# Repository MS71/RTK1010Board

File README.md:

# RTK1010Board

Arduino Compatible RTK1010 Board/PCB

**:exclamation: Design not finished yet :exclamation:**

### Features:

- Arduino compatibe form factor
- RTK1010 GPS receiver
- IPEX connector for onboard antennas
- backup battery
- optional SMA connector for external antennas
- optional LDO for LNA power supply
- optional ESP32-S2 for operating as base station
- optional power via USB
- optional IMU (BNO055)

### Use Cases:

#### A) Minimum RTK-1010 receiver with arduino form factor

  - RTK-1010 <-> RX/TX arduino pins
  - SMA or IPEX connector
  - LNA power by RTK-1010 (max 30mA)
  - RTK-1010 backup battery
  - *(optional)* LNA LDO (max 250mA)

#### B) Minimum RTK base station with RTK-1010 & ESP32-S2 powered by USB

  - ESP32: RTK <=> TCP bridge
  - powered by USB
  - SMA or IPEX connector
  - LNA power
  - RTK-1010 backup battery
  - *(optional)* LNA LDO (max 250mA)

#### C) Mowgli HEAD with RTK-1010, ESP32-S2 and IMU - *(TODO)*

  - ESP32: running microROS
  - VCC, GND, UART interface to YF mainboard
  - low power, sleep mode

---

[Build Manual](BuildManual.pdf)

For the [BOM](bom/README.md) take a look at the [bom folder](bom/) - *there is also an [iBOM](bom/ibom.html) available*

[RTK 1010 datasheet](https://www.locosystech.com/Templates/att/RTK-1010_datasheet_v0.7.pdf)

[Schematic](kicad/RTK1010Board.pdf)

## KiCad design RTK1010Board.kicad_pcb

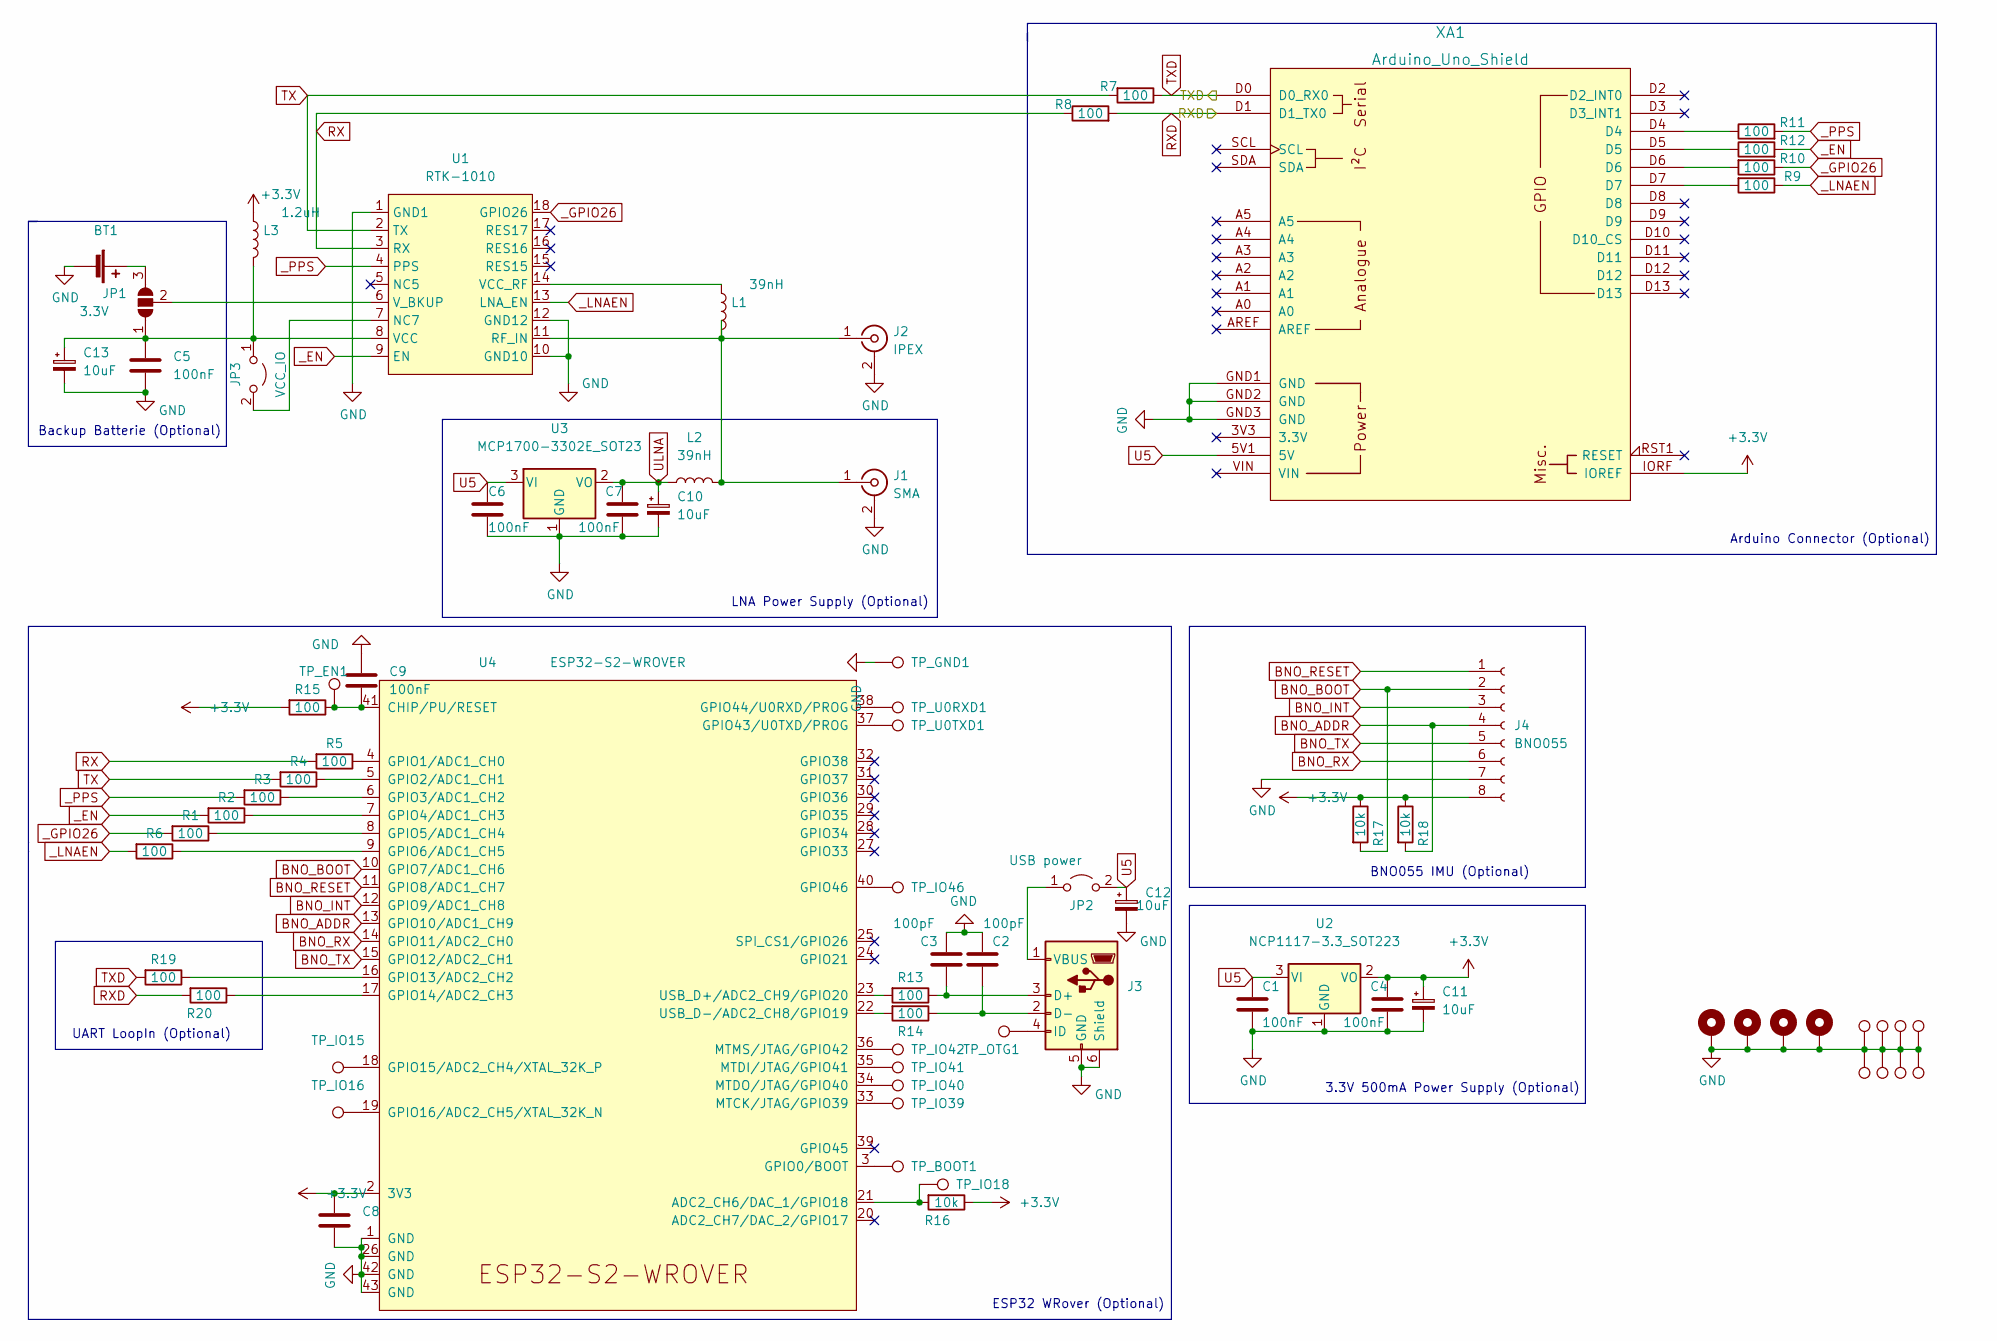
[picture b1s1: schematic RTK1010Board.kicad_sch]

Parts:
BT1: 3.3V; BatteryHolder_Keystone_1058_1x2032
C1, C4, C5, C6, C7, C8, C9: 100nF; C_0805_2012Metric_Pad1.18x1.45mm_HandSolder
C2, C3: 100pF; C_0805_2012Metric_Pad1.18x1.45mm_HandSolder
C10, C11, C12, C13: 10uF; CP_EIA-7132-20_AVX-U_Pad2.72x3.50mm_HandSolder
H1, H2, H3, H4: MountingHole_Pad; MountingHole_3.2mm_M3_DIN965_Pad
J1: SMA; SMA_Amphenol_132134-11_Vertical
J2: IPEX; U.FL_Molex_MCRF_73412-0110_Vertical
J3: USB_OTG; USB_Micro-B_Amphenol_10118194_Horizontal
J4: BNO055; PinSocket_1x08_P2.54mm_Vertical_SMD_Pin1Right
JP1: SolderJumper_3_Open; SolderJumper-3_P1.3mm_Open_RoundedPad1.0x1.5mm
JP2: USB power; SolderJumper-2_P1.3mm_Open_RoundedPad1.0x1.5mm
JP3: VCC_IO; SolderJumper-2_P1.3mm_Open_RoundedPad1.0x1.5mm
L1, L2: 39nH; L_0805_2012Metric_Pad1.15x1.40mm_HandSolder
L3: 1.2uH; L_0805_2012Metric_Pad1.15x1.40mm_HandSolder
R1, R2, R3, R4, R5, R6, R7, R8, R9, R10, R11, R12, R13, R14, R15, R19, R20: 100; R_0805_2012Metric_Pad1.20x1.40mm_HandSolder
R16, R17, R18: 10k; R_0805_2012Metric_Pad1.20x1.40mm_HandSolder
TP1, TP2, TP3, TP4, TP5, TP6, TP7, TP8: TestPoint; TestPoint_Loop_D2.50mm_Drill1.0mm
TP_BOOT1: TestPoint; TestPoint_Pad_D2.0mm
TP_EN1: TestPoint; TestPoint_Pad_D2.0mm
TP_GND1: TestPoint; TestPoint_Pad_D2.0mm
TP_IO15, TP_IO16, TP_IO18, TP_IO39, TP_IO40, TP_IO41, TP_IO42, TP_IO46: TestPoint; TestPoint_Pad_D2.0mm
TP_OTG1: TestPoint; TestPoint_Pad_D2.0mm
TP_U0RXD1, TP_U0TXD1: TestPoint; TestPoint_Pad_D2.0mm
U1: RTK-1010; rtk1010
U2: NCP1117-3.3_SOT223; SOT-223-3_TabPin2
U3: MCP1700-3302E_SOT23; SOT-23
U4: ESP32-S2-WROVER
XA1: Arduino_Uno_Shield

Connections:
+3V3: C4.1, C8.1, C11.1, J4.8, L3.1, R15.2, R16.1, R17.1, R18.1, U2.2 (VO), U4.2 (3V3), XA1.IORF (IOREF)
BNO_ADDR: J4.4, R18.2, U4.13 (GPIO10/ADC1_CH9)
BNO_BOOT: J4.2, R17.2, U4.10 (GPIO7/ADC1_CH6)
BNO_INT: J4.3, U4.12 (GPIO9/ADC1_CH8)
BNO_RESET: J4.1, U4.11 (GPIO8/ADC1_CH7)
BNO_RX: J4.6, U4.14 (GPIO11/ADC2_CH0)
BNO_TX: J4.5, U4.15 (GPIO12/ADC2_CH1)
GND: BT1.2 (-), C1.2, C2.1, C3.1, C4.2, C5.2, C6.2, C7.2, C8.2, C9.1, C10.2, C11.2, C12.2, C13.2, H1.1, H2.1, H3.1, H4.1, J1.2 (Ext), J2.2 (Ext), J3.5 (GND), J3.6 (Shield), J4.7, TP1.1, TP2.1, TP3.1, TP4.1, TP5.1, TP6.1, TP7.1, TP8.1, TP_GND1.1, U1.1 (GND1), U1.10 (GND10), U1.12 (GND12), U2.1 (GND), U3.1 (GND), U4.1 (GND), U4.26 (GND), U4.42 (GND), U4.43 (GND), XA1.GND1 (GND), XA1.GND2 (GND), XA1.GND3 (GND)
unnamed: BT1.1 (+), JP1.3 (B)
unnamed: C2.2, J3.2 (D-), R14.1
unnamed: C3.2, J3.3 (D+), R13.1
unnamed: C9.2, R15.1, TP_EN1.1, U4.41 (CHIP/PU/RESET)
unnamed: C5.1, C13.1, JP1.1 (A), JP3.1 (A), L3.2, U1.8 (VCC)
unnamed: J1.1 (In), J2.1 (In), L1.2, L2.2, U1.11 (RF_IN)
unnamed: J3.1 (VBUS), JP2.1 (A)
unnamed: J3.4 (ID), TP_OTG1.1
unnamed: JP1.2 (C), U1.6 (V_BKUP)
unnamed: JP3.2 (B), U1.7 (NC7)
unnamed: L1.1, U1.14 (VCC_RF)
unnamed: R1.1, U4.8 (GPIO5/ADC1_CH4)
unnamed: R2.1, U4.7 (GPIO4/ADC1_CH3)
unnamed: R3.1, U4.6 (GPIO3/ADC1_CH2)
unnamed: R4.1, U4.5 (GPIO2/ADC1_CH1)
unnamed: R5.1, U4.4 (GPIO1/ADC1_CH0)
unnamed: R6.1, U4.9 (GPIO6/ADC1_CH5)
unnamed: R9.2, XA1.D7
unnamed: R10.2, XA1.D6
unnamed: R11.1, XA1.D4
unnamed: R12.1, XA1.D5
unnamed: R13.2, U4.23 (USB_D+/ADC2_CH9/GPIO20)
unnamed: R14.2, U4.22 (USB_D-/ADC2_CH8/GPIO19)
unnamed: R16.2, TP_IO18.1, U4.21 (ADC2_CH6/DAC_1/GPIO18)
unnamed: R19.1, U4.16 (GPIO13/ADC2_CH2)
unnamed: R20.1, U4.17 (GPIO14/ADC2_CH3)
unnamed: TP_BOOT1.1, U4.3 (GPIO0/BOOT)
unnamed: TP_IO15.1, U4.18 (GPIO15/ADC2_CH4/XTAL_32K_P)
unnamed: TP_IO16.1, U4.19 (GPIO16/ADC2_CH5/XTAL_32K_N)
unnamed: TP_IO39.1, U4.33 (MTCK/JTAG/GPIO39)
unnamed: TP_IO40.1, U4.34 (MTDO/JTAG/GPIO40)
unnamed: TP_IO41.1, U4.35 (MTDI/JTAG/GPIO41)
unnamed: TP_IO42.1, U4.36 (MTMS/JTAG/GPIO42)
unnamed: TP_IO46.1, U4.40 (GPIO46)
unnamed: TP_U0RXD1.1, U4.38 (GPIO44/U0RXD/PROG)
unnamed: TP_U0TXD1.1, U4.37 (GPIO43/U0TXD/PROG)
RX: R5.2, R8.1, U1.3 (RX)
RXD: R8.2, R20.2, XA1.D1 (D1_TX0)
TX: R4.2, R7.2, U1.2 (TX)
TXD: R7.1, R19.2, XA1.D0 (D0_RX0)
U5: C1.1, C6.1, C12.1, JP2.2 (B), U2.3 (VI), U3.3 (VI), XA1.5V1 (5V)
ULNA: C7.1, C10.1, L2.1, U3.2 (VO)
_EN: R2.2, R12.2, U1.9 (EN)
_GPIO26: R1.2, R10.1, U1.18 (GPIO26)
_LNAEN: R6.2, R9.1, U1.13 (LNA_EN)
_PPS: R3.2, R11.2, U1.4 (PPS)

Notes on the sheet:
ESP32 WRover (Optional)
Arduino Connector (Optional)
LNA Power Supply (Optional)
3.3V 500mA Power Supply (Optional)
BNO055 IMU (Optional)
Backup Batterie (Optional)
UART LoopIn (Optional)

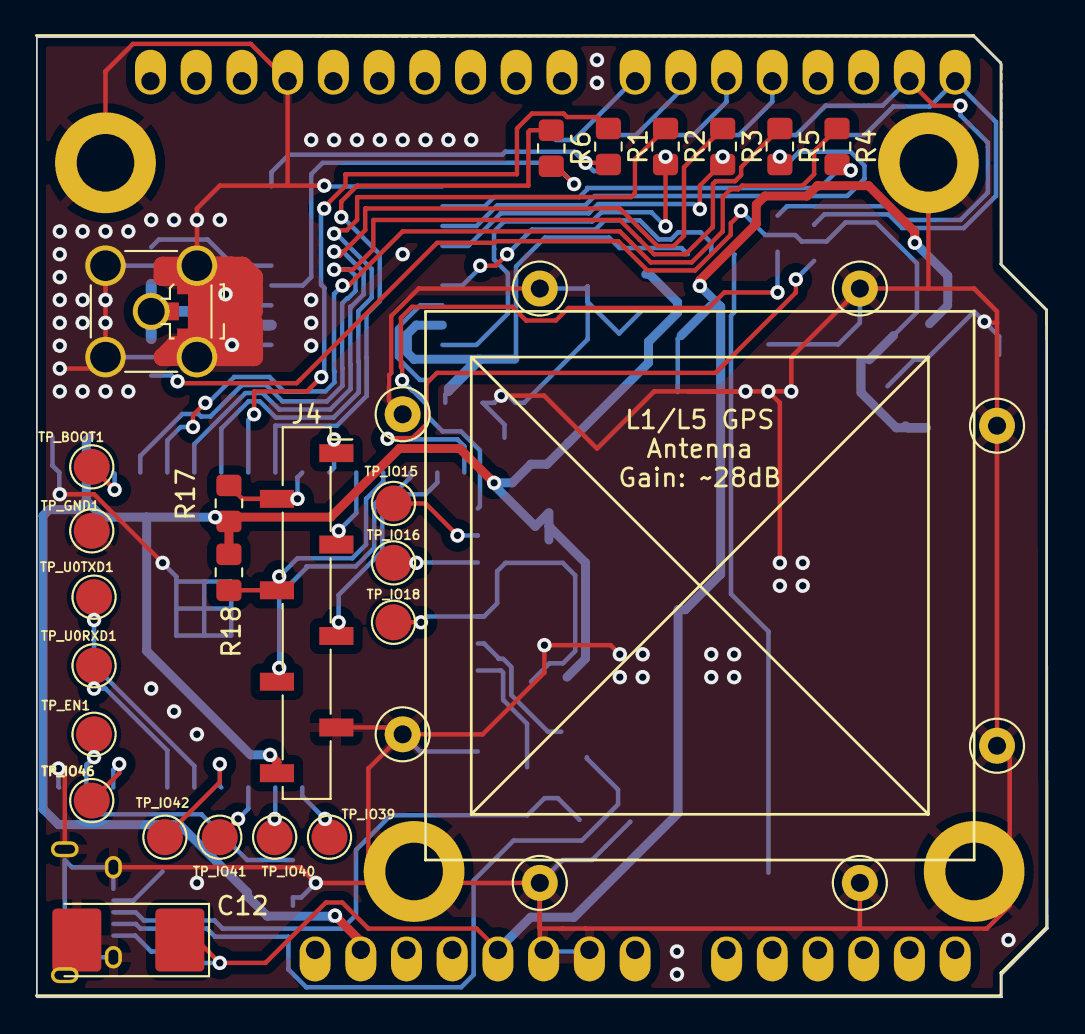
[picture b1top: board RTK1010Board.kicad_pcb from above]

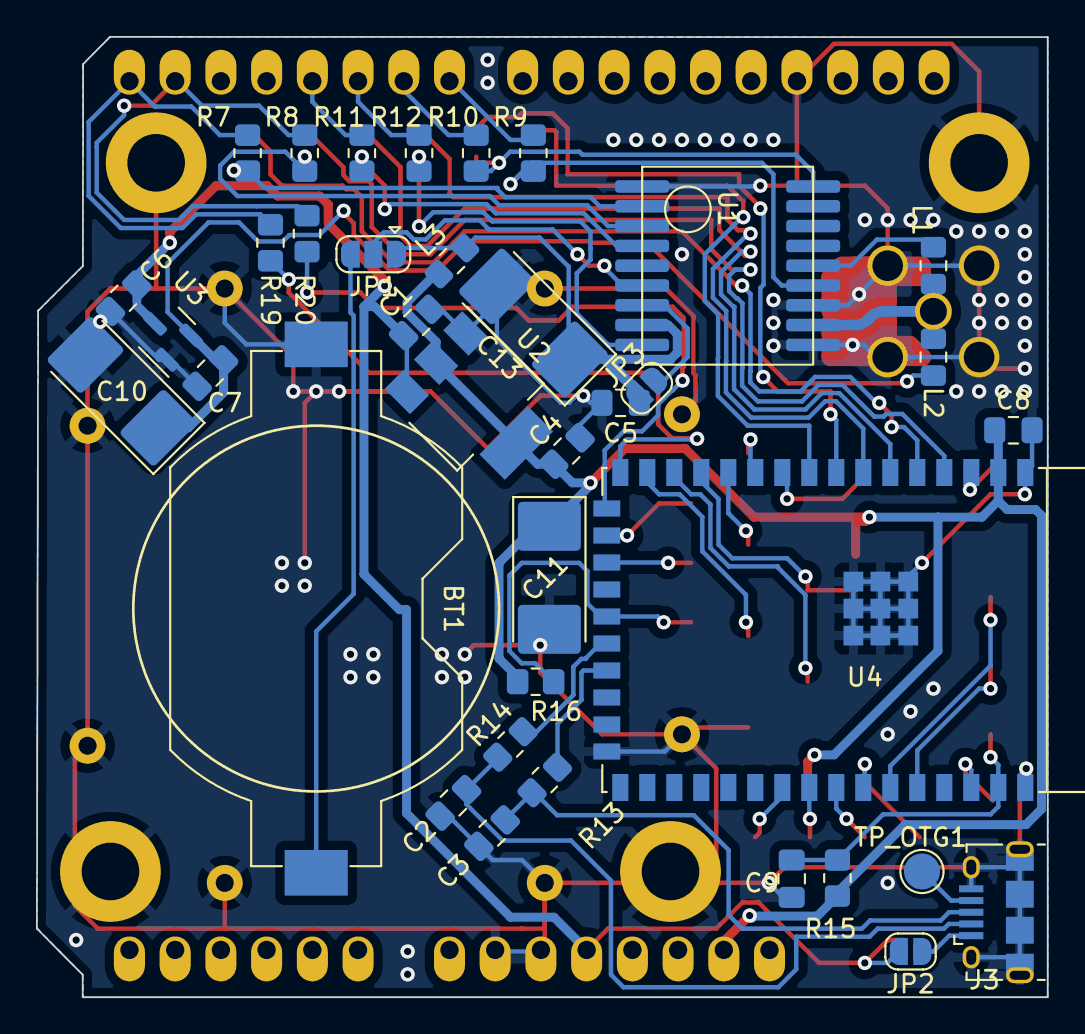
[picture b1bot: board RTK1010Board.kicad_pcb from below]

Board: 2 copper layers, 56.2 x 53.3 mm, 75 parts (37 on the bottom side), 54 nets.

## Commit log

2022-08-08 first version
2022-08-08 pdf and images added
2022-08-08 schematic image added
2022-08-08 gerber files added
2022-08-08 ESP32-S2 mini replaced by WROVER module
2022-08-08 gerber files created
2022-08-08 some more small changes
2022-08-14 bno055 added
2022-08-17 UART LoopIn option added USB connected to USB pins
2022-08-17 boot image added
2022-08-19 some optimiziations implemented
2022-08-21 RTK1010 VCC LP filter added
2022-08-25 Jefs comments implemented
2022-08-25 some vias added
2022-08-25 some minor changes
2022-08-27 LDO replaced by 500ma type
2022-09-03 support for teseo-liv3fl added
2022-09-06 ibom added
2022-09-06 ibom improved
2022-09-06 ibom updated
2022-09-08 V1.0
2022-09-25 added
2022-10-01 buildmanual updated
2022-10-24 esp32_fw added
2022-11-29 latest work
2023-01-12 bom added
2023-01-12 R16 removed
2023-01-12 R16 added
2023-01-12 mode jumper added
2023-01-12 LNA LDO option added
2023-01-22 change usb docket links
2023-01-22 ibom update
2023-01-22 some cosmetic changes
2023-01-22 some build instructions added
2023-01-29 ota added
2023-01-29 README updated
2023-02-12 rtcm filter added
2023-02-16 add: vscode workspace
2023-02-19 bom update - optional U2 at config C)
2023-02-19 fix: typos
2023-02-19 nmealib removed first time GTKFix handled by ESP
2023-02-19 some function header added
2023-03-05 CONFIG_RTK1010_NODE_BASE_RTCM_SERVER implemented
2023-03-06 rtcm client mode implemented
2023-03-06 rtcm server mode, nmea disabled
2023-03-06 rtcm client mode improved
2023-04-07 gps_md.uart.initflag added
2023-04-07 CONFIG_RTCM_SERVER_BASEXYZ option added
2023-04-11 lla2ecef conversion added
2023-04-11 rtk boot time sleep changed
2023-04-11 en reboot time changed#
2023-04-11 ddmmtodd removed for att
2023-05-16 CONFIG_RTK1010_NODE_PASS_TO_CDC added
2023-05-16 CONFIG_RTK1010_NODE_CDC_ADAPTER implemented
2023-05-24 passing tcpclient correction data only with fix added
2023-05-28 BASEXYZ automatic mode implemented
2023-05-30 compile issue fixed and auto save config added when fix is increasing
2023-06-03 CONFIG_CUSTOM_CMD_SEQUENCE_0 added
2023-07-15 Update BOM: - update tantalum to fit footprint - add alternative U3 part - add antennas section - cosmetic changes - switch format patly to html
2023-08-13 gps RTCM_THROTTLING_PERIOD added
2023-08-27 Add Linx ANT-GNRM-L15A series antenna
2024-06-02 hdop value added
